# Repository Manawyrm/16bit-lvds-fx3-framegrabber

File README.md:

# Cypress FX3-based 16bit LVDS Framegrabber (Hardware repo)

### Overview

The 16bit-LVDS-FX3-Framegrabber is a Cypress FX3-based PCB, which can digitize a parallel 16bit digital video stream from a commercial image sensor.
It exposes a USB 3.0 UVC ("webcam") device to the operating system.

Video signal is accepted on a 50pin SCSI-II connector as parallel LVDS.  
Required signals:
- DATA_VALID
- HSYNC
- VSYNC
- PIXCLK
- DATA0 through DATA15

The framegrabber follows the common industry standard pinout for 16bit digital LVDS video.

### Errata
None so far. Rev. A works well.

### Additional info 
[Firmware](https://github.com/Manawyrm/16bit-lvds-fx3-framegrabber-fw)

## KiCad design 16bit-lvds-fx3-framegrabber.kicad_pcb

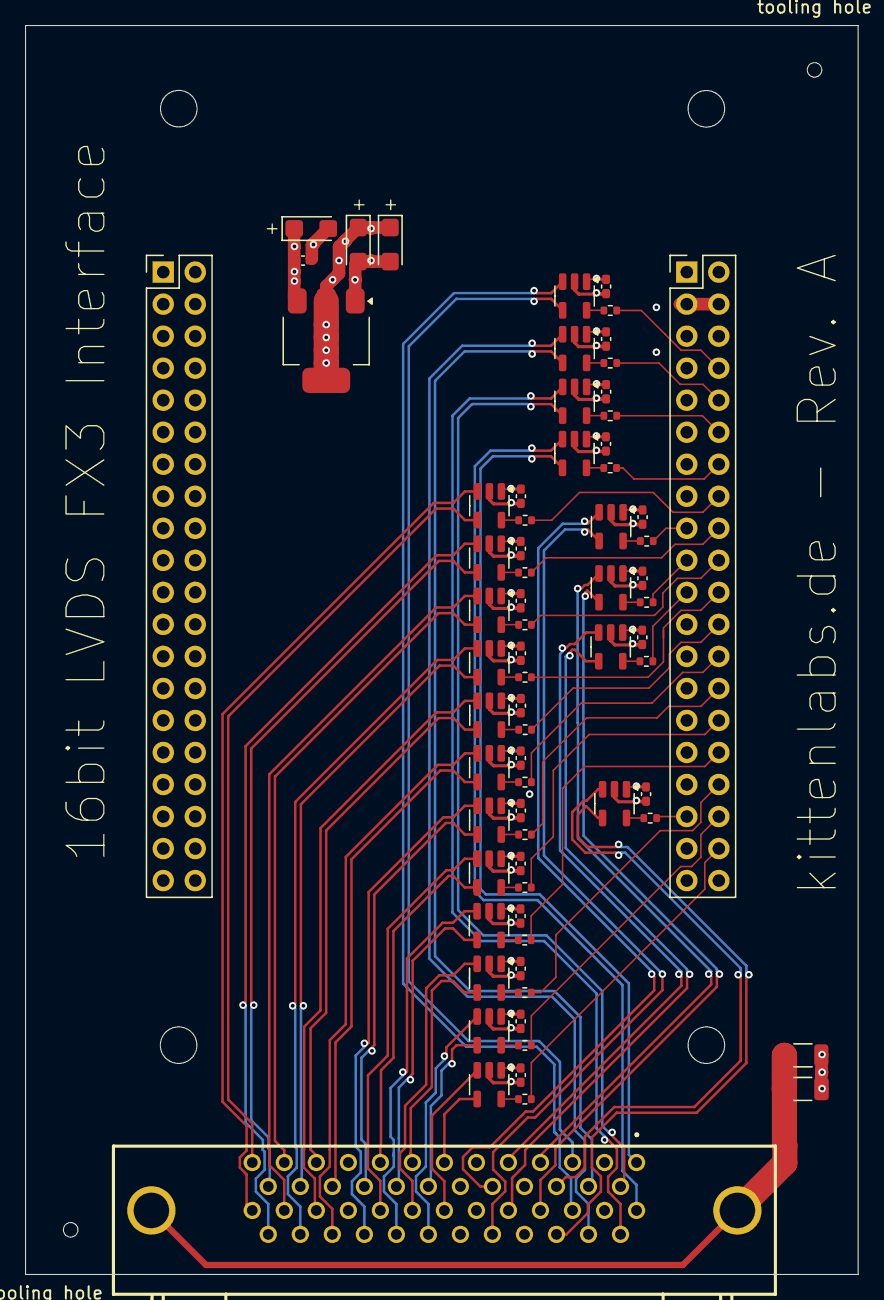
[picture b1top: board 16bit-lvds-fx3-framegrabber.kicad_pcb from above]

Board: 4 copper layers, 66.0 x 99.1 mm, 72 parts (0 on the bottom side), 81 nets.

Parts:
C1, C3, C4, C5, C6, C7, C8, C9, C10, C11, C12, C13, C14, C15, C16, C17, C18, C19, C20, C21, C22: 100n 16V; C_0402_1005Metric_Pad0.74x0.62mm_HandSolder
C2: 2kV 1nF; C_1206_3216Metric
C23, C24, C25: 10uF 16V; CP_EIA-3216-10_Kemet-I
H1, H2: MountingHole; ToolingHole_JLCSMT
J1: GPIFII_J7; PinHeader_2x20_P2.54mm_Vertical
J2: GPIFII_J6; PinHeader_2x20_P2.54mm_Vertical
R1: 100k; R_1206_3216Metric
R2, R3, R4, R5, R6, R7, R8, R9, R10, R11, R12, R13, R14, R15, R16, R17, R18, R19, R20, R21: 33R; R_0402_1005Metric
U1: 5787082-5; DSUB-TH_5787082-5
U2, U3, U4, U5, U6, U7, U8, U9, U10, U11, U12, U13, U14, U15, U16, U17, U18, U19, U20, U21: SN65LVDT2DBV; SOT-23-5
U22: AMS1117-3.3; SOT-223-3_TabPin2

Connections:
+3V3: C1.1, C3.1, C4.1, C5.1, C6.1, C7.1, C8.1, C9.1, C10.1, C11.1, C12.1, C13.1, C14.1, C15.1, C16.1, C17.1, C18.1, C19.1, C20.1, C21.1, C23.1, C24.1, U2.1 (V_{CC}), U3.1 (V_{CC}), U4.1 (V_{CC}), U5.1 (V_{CC}), U6.1 (V_{CC}), U7.1 (V_{CC}), U8.1 (V_{CC}), U9.1 (V_{CC}), U10.1 (V_{CC}), U11.1 (V_{CC}), U12.1 (V_{CC}), U13.1 (V_{CC}), U14.1 (V_{CC}), U15.1 (V_{CC}), U16.1 (V_{CC}), U17.1 (V_{CC}), U18.1 (V_{CC}), U19.1 (V_{CC}), U20.1 (V_{CC}), U21.1 (V_{CC}), U22.2 (VO)
+5V: C22.1, C25.1, J2.3 (USB3_VBUS), J2.4 (USB3_VBUS), U22.3 (VI)
/DATA_VALID: J2.17 (CTL7), R20.2
/DATA_VALID+: U1.10, U20.3 (A)
/DATA_VALID-: U1.35, U20.4 (B)
/HSYNC: J2.19 (CTL6), R18.2
/HSYNC+: U1.7, U18.3 (A)
/HSYNC-: U1.32, U18.4 (B)
/OUT0: J2.38 (DQ0), R2.2
/OUT0+: U1.38, U2.3 (A)
/OUT0-: U1.13, U2.4 (B)
/OUT1: J2.36 (DQ1), R3.2
/OUT1+: U1.39, U3.3 (A)
/OUT1-: U1.14, U3.4 (B)
/OUT2: J2.34 (DQ2), R4.2
/OUT2+: U1.40, U4.3 (A)
/OUT2-: U1.15, U4.4 (B)
/OUT3: J2.32 (DQ3), R5.2
/OUT3+: U1.41, U5.3 (A)
/OUT3-: U1.16, U5.4 (B)
/OUT4: J2.30 (DQ4), R6.2
/OUT4+: U1.42, U6.3 (A)
/OUT4-: U1.17, U6.4 (B)
/OUT5: J2.28 (DQ5), R7.2
/OUT5+: U1.43, U7.3 (A)
/OUT5-: U1.18, U7.4 (B)
/OUT6: J2.26 (DQ6), R8.2
/OUT6+: U1.45, U8.3 (A)
/OUT6-: U1.20, U8.4 (B)
/OUT8: J2.22 (DQ8), R10.2
/OUT8+: U1.47, U10.3 (A)
/OUT8-: U1.22, U10.4 (B)
/OUT9: J2.20 (DQ9), R11.2
/OUT9+: U1.48, U11.3 (A)
/OUT9-: U1.23, U11.4 (B)
/OUT10: J2.18 (DQ10), R12.2
/OUT10+: U1.49, U12.3 (A)
/OUT10-: U1.24, U12.4 (B)
/OUT11: J2.16 (DQ11), R13.2
/OUT11+: U1.50, U13.3 (A)
/OUT11-: U1.25, U13.4 (B)
/OUT12: J2.14 (DQ12), R14.2
/OUT12+: U1.26, U14.3 (A)
/OUT12-: U1.1, U14.4 (B)
/OUT13: J2.12 (DQ13), R15.2
/OUT13+: U1.27, U15.3 (A)
/OUT13-: U1.2, U15.4 (B)
/OUT14: J2.10 (DQ14), R16.2
/OUT14+: U1.29, U16.3 (A)
/OUT14-: U1.4, U16.4 (B)
/OUT15: J2.8 (DQ15), R17.2
/OUT15+: U1.30, U17.3 (A)
/OUT15-: U1.5, U17.4 (B)
/PIXCLK: J2.35 (PCLK), R21.2
/PIXCLK+: U1.6, U21.3 (A)
/PIXCLK-: U1.31, U21.4 (B)
/VSYNC: J2.21 (CTL5), R19.2
/VSYNC+: U1.9, U19.3 (A)
/VSYNC-: U1.34, U19.4 (B)
GND: C1.2, C2.2, C3.2, C4.2, C5.2, C6.2, C7.2, C8.2, C9.2, C10.2, C11.2, C12.2, C13.2, C14.2, C15.2, C16.2, C17.2, C18.2, C19.2, C20.2, C21.2, C22.2, C23.2, C24.2, C25.2, J1.13 (GND), J1.15 (GND), J1.17 (GND), J1.25 (GND), J1.29 (GND), J1.39 (GND), J1.40 (GND), J2.6 (GND), J2.33 (GND), J2.37 (GND), R1.2, U1.3, U1.8, U1.19, U1.28, U1.33, U1.44, U2.2 (GND), U3.2 (GND), U4.2 (GND), U5.2 (GND), U6.2 (GND), U7.2 (GND), U8.2 (GND), U9.2 (GND), U10.2 (GND), U11.2 (GND), U12.2 (GND), U13.2 (GND), U14.2 (GND), U15.2 (GND), U16.2 (GND), U17.2 (GND), U18.2 (GND), U19.2 (GND), U20.2 (GND), U21.2 (GND), U22.1 (GND)
unnamed: C2.1, R1.1, U1.S1, U1.S2
unnamed: R2.1, U2.5 (R)
unnamed: R3.1, U3.5 (R)
unnamed: R4.1, U4.5 (R)
unnamed: R5.1, U5.5 (R)
unnamed: R6.1, U6.5 (R)
unnamed: R7.1, U7.5 (R)
unnamed: R8.1, U8.5 (R)
unnamed: R9.1, U9.5 (R)
unnamed: R10.1, U10.5 (R)
unnamed: R11.1, U11.5 (R)
unnamed: R12.1, U12.5 (R)
unnamed: R13.1, U13.5 (R)
unnamed: R14.1, U14.5 (R)
unnamed: R15.1, U15.5 (R)
unnamed: R16.1, U16.5 (R)
unnamed: R17.1, U17.5 (R)
unnamed: R18.1, U18.5 (R)
unnamed: R19.1, U19.5 (R)
unnamed: R20.1, U20.5 (R)
unnamed: R21.1, U21.5 (R)

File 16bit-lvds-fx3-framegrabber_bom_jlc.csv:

"Comment","Designator","Footprint","LCSC Part Number"
"2kV 1nF","C2","C_1206_3216Metric","C9196"
"100n 16V","C22,C1,C3,C4,C5,C6,C7,C8,C9,C10,C11,C12,C13,C14,C15,C16,C17,C18,C19,C20,C21","C_0402_1005Metric_Pad0.74x0.62mm_HandSolder","C1525"
"10uF 16V","C23,C24,C25","CP_EIA-3216-10_Kemet-I","C7171"
"GPIFII_J7","J1","PinHeader_2x20_P2.54mm_Vertical","C50980"
"GPIFII_J6","J2","PinHeader_2x20_P2.54mm_Vertical","C50980"
"100k","R1","R_1206_3216Metric","C17900"
"33R","R2,R3,R4,R5,R6,R7,R8,R9,R10,R11,R12,R13,R14,R15,R16,R17,R18,R19,R20,R21","R_0402_1005Metric","C25105"
"5787082-5","U1","DSUB-TH_5787082-5","C3119894"
"SN65LVDT2DBV","U2,U3,U4,U5,U6,U7,U8,U9,U10,U11,U12,U13,U14,U15,U16,U17,U18,U19,U20,U21","SOT-23-5","C130020"
"AMS1117-3.3","U22","SOT-223-3_TabPin2","C6186"
